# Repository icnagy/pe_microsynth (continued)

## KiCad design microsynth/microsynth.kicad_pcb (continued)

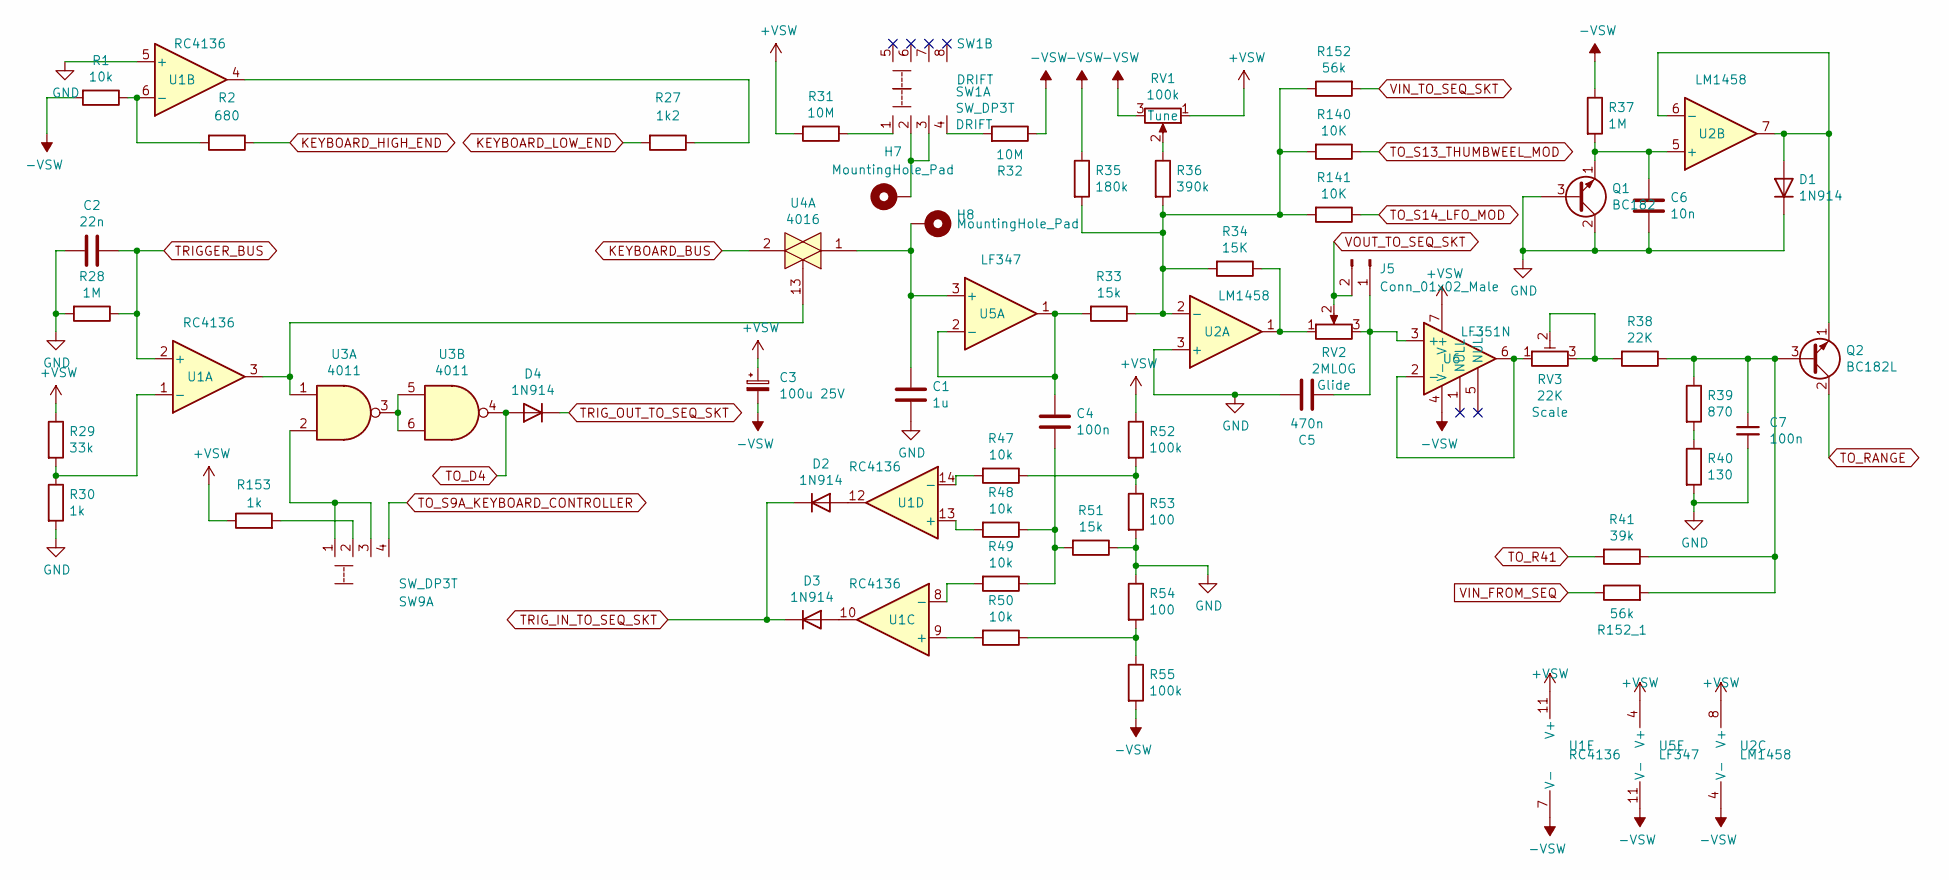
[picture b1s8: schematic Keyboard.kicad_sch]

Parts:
C1: 1u; C_Rect_L7.2mm_W7.2mm_P5.00mm_FKS2_FKP2_MKS2_MKP2
C2: 22n; C_Rect_L7.2mm_W2.5mm_P5.00mm_FKS2_FKP2_MKS2_MKP2
C3: 100u 25V; CP_Radial_D5.0mm_P2.50mm
C4, C7: 100n; C_Rect_L7.2mm_W2.5mm_P5.00mm_FKS2_FKP2_MKS2_MKP2
C5: 470n; C_Rect_L7.2mm_W4.5mm_P5.00mm_FKS2_FKP2_MKS2_MKP2
C6: 10n; C_Rect_L7.2mm_W2.5mm_P5.00mm_FKS2_FKP2_MKS2_MKP2
D1, D2, D3, D4: 1N914; D_DO-35_SOD27_P7.62mm_Horizontal
H7, H8: MountingHole_Pad; PinHeader_1x01_P2.54mm_Vertical
J5: Conn_01x02_Male; PinHeader_1x02_P2.54mm_Vertical
Q1: BC182; TO-92L_Inline_Wide
Q2: BC182L; TO-92L_Inline_Wide
R1, R47, R48, R49, R50: 10k; R_Axial_DIN0207_L6.3mm_D2.5mm_P10.16mm_Horizontal
R2: 680; R_Axial_DIN0207_L6.3mm_D2.5mm_P10.16mm_Horizontal
R27: 1k2; R_Axial_DIN0207_L6.3mm_D2.5mm_P10.16mm_Horizontal
R28, R37: 1M; R_Axial_DIN0207_L6.3mm_D2.5mm_P10.16mm_Horizontal
R29: 33k; R_Axial_DIN0207_L6.3mm_D2.5mm_P10.16mm_Horizontal
R30, R153: 1k; R_Axial_DIN0207_L6.3mm_D2.5mm_P10.16mm_Horizontal
R31, R32: 10M; R_Axial_DIN0207_L6.3mm_D2.5mm_P10.16mm_Horizontal
R33, R51: 15k; R_Axial_DIN0207_L6.3mm_D2.5mm_P10.16mm_Horizontal
R34: 15K; R_Axial_DIN0207_L6.3mm_D2.5mm_P10.16mm_Horizontal
R35: 180k; R_Axial_DIN0207_L6.3mm_D2.5mm_P10.16mm_Horizontal
R36: 390k; R_Axial_DIN0207_L6.3mm_D2.5mm_P10.16mm_Horizontal
R38: 22K; R_Axial_DIN0207_L6.3mm_D2.5mm_P10.16mm_Horizontal
R39: 870; R_Axial_DIN0207_L6.3mm_D2.5mm_P10.16mm_Horizontal
R40: 130; R_Axial_DIN0207_L6.3mm_D2.5mm_P10.16mm_Horizontal
R41: 39k; R_Axial_DIN0207_L6.3mm_D2.5mm_P10.16mm_Horizontal
R52, R55: 100k; R_Axial_DIN0207_L6.3mm_D2.5mm_P10.16mm_Horizontal
R53, R54: 100; R_Axial_DIN0207_L6.3mm_D2.5mm_P10.16mm_Horizontal
R140, R141: 10K; R_Axial_DIN0207_L6.3mm_D2.5mm_P10.16mm_Horizontal
R152, R152_1: 56k; R_Axial_DIN0207_L6.3mm_D2.5mm_P10.16mm_Horizontal
RV1: 100k; Potentiometer_Bourns_3296W_Vertical
RV2: 2MLOG; Pot_16mm_NoDet_RV16AF-4A
RV3: 22K; Potentiometer_Bourns_3296W_Vertical
SW1: SW_DP3T; 11-SS-23-832C
SW9: TRIGGER; 11-SS-23-832C
U1: RC4136; DIP-14_W7.62mm_LongPads
U2: LM1458; DIP-8_W7.62mm_LongPads
U3: 4011; DIP-14_W7.62mm_LongPads
U4: 4016; DIP-14_W7.62mm_LongPads
U5: LF347; DIP-14_W7.62mm_LongPads
U6: LF351N; DIP-8_W7.62mm_LongPads

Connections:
+VSW: C3.1, R29.1, R31.2, R52.1, R153.1, RV1.1, U1.11 (V+), U2.8 (V+), U5.4 (V+), U6.7 (V+); also elsewhere on the board
-VSW: C3.2, R1.2, R32.1, R35.1, R37.1, R55.2, RV1.3, U1.7 (V-), U2.4 (V-), U5.11 (V-), U6.4 (V-); also elsewhere on the board
GND: C1.2, C2.2, C5.2, C6.2, C7.2, D1.1 (K), Q1.2 (C), Q1.3 (B), R28.2, R30.2, R40.2, R51.1, R53.2, R54.1, U1.5 (+), U2.3 (+); also elsewhere on the board
KEYBOARD_BUS: U4.2; also elsewhere on the board
KEYBOARD_HIGH_END: R2.1; also elsewhere on the board
KEYBOARD_LOW_END: R27.2; also elsewhere on the board
unnamed: C1.1, H8.1, U4.1, U5.3 (+)
unnamed: C4.1, R33.2, U5.1, U5.2 (-)
unnamed: C4.2, R48.1, R49.1, R51.2
unnamed: C5.1, J5.1, RV2.3, U6.3 (+)
unnamed: C6.1, Q1.1 (E), R37.2, U2.5 (+)
unnamed: C7.1, Q2.3 (B), R38.1, R39.1, R41.1, R152_1.2
unnamed: D1.2 (A), Q2.1 (E), U2.6 (-), U2.7
unnamed: D2.2 (A), U1.12
unnamed: D3.2 (A), U1.10
unnamed: H7.1, SW1.2, SW1.3
unnamed: R1.1, R2.2, U1.6 (-)
unnamed: R27.1, U1.4
unnamed: R29.2, R30.1, U1.1 (-)
unnamed: R31.1, SW1.1
unnamed: R32.2, SW1.4
unnamed: R34.1, RV2.1, U2.1
unnamed: R36.1, RV1.2
unnamed: R38.2, RV3.2, RV3.3
unnamed: R39.2, R40.1
unnamed: R47.1, R52.2, R53.1
unnamed: R47.2, U1.14 (-)
unnamed: R48.2, U1.13 (+)
unnamed: R49.2, U1.8 (-)
unnamed: R50.1, R54.2, R55.1
unnamed: R50.2, U1.9 (+)
unnamed: R33.1, R34.2, R35.2, R36.2, R140.2, R141.2, R152.1, U2.2 (-)
unnamed: R153.2, SW9.2
unnamed: RV3.1, U6.2 (-), U6.6
unnamed: SW9.1, SW9.3, U3.2
unnamed: U1.3, U3.1, U4.13
unnamed: U3.3, U3.5, U3.6
S5_VCO2: SW9.4; also elsewhere on the board
TO_D4: D4.2 (A), U3.4; also elsewhere on the board
TO_KBD_R140: R140.1; also elsewhere on the board
TO_KBD_R141: R141.1; also elsewhere on the board
TO_R41: R41.2; also elsewhere on the board
TO_RANGE: Q2.2 (C); also elsewhere on the board
TRIGGER_BUS: C2.1, R28.1, U1.2 (+); also elsewhere on the board
TRIG_IN_TO_SEQ_SKT: D2.1 (K), D3.1 (K); also elsewhere on the board
TRIG_OUT_TO_SEQ_SKT: D4.1 (K); also elsewhere on the board
VIN_FROM_SEQ: R152_1.1; also elsewhere on the board
VIN_TO_SEQ_SKT: R152.2; also elsewhere on the board
VOUT_TO_SEQ_SKT: J5.2, RV2.2; also elsewhere on the board

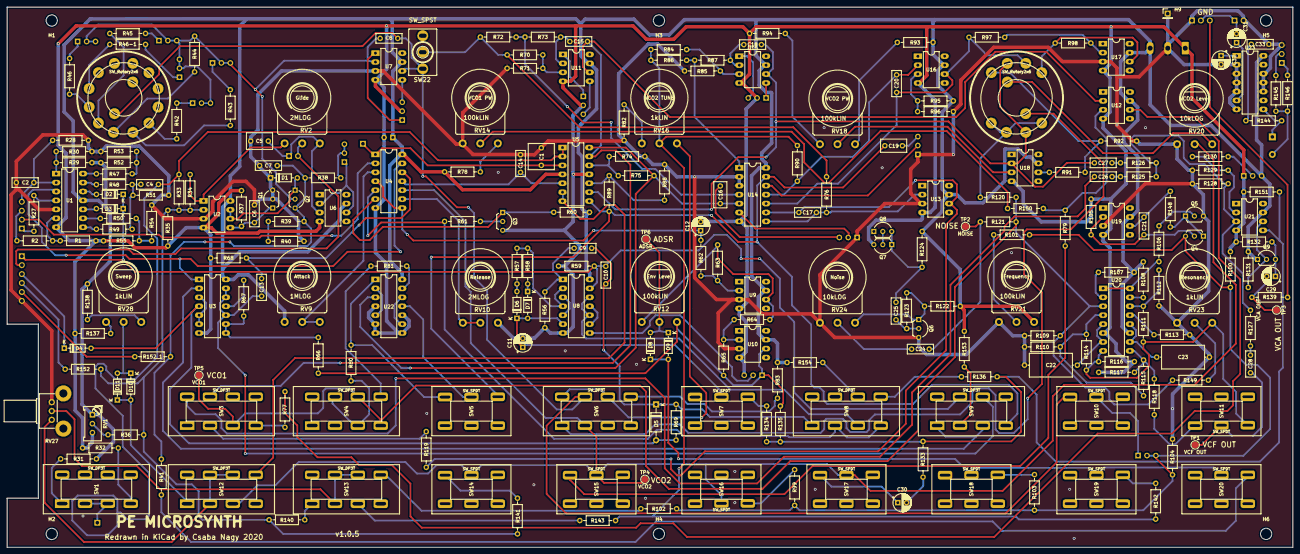
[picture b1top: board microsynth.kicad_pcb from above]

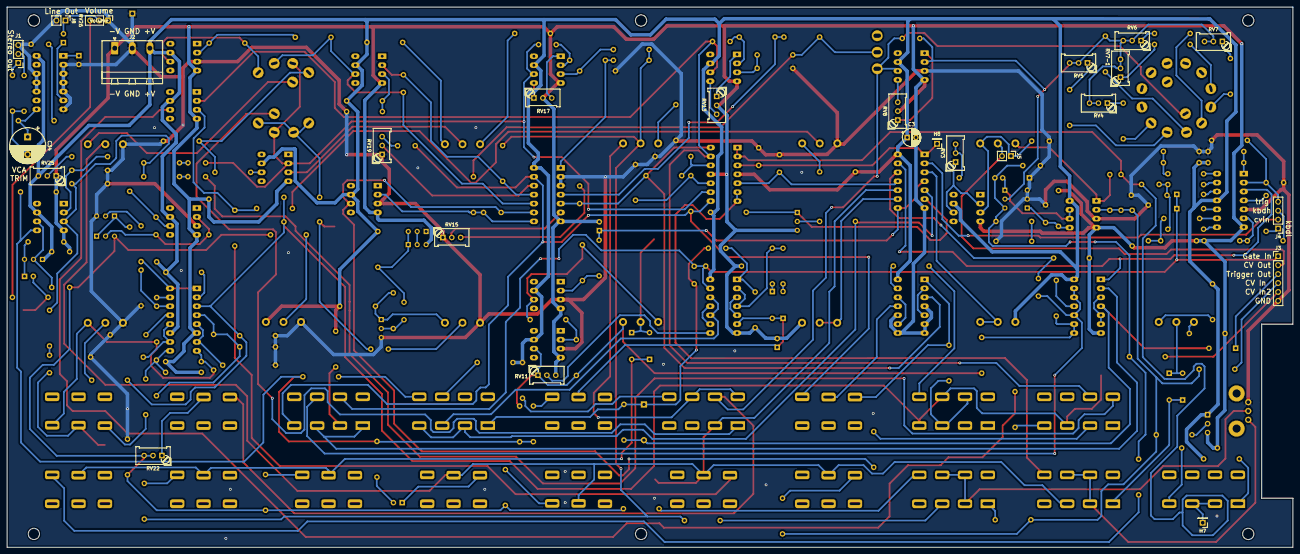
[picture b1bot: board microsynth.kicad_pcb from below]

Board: 2 copper layers, 365.8 x 153.7 mm, 280 parts (25 on the bottom side), 208 nets.

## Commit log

2020-03-30 Footprints
2020-04-01 Footprints 2
2020-04-01 Hacking together the footprints
2020-04-03 All components placed on PCB
2020-04-03 Add front panel design
2020-04-03 Aligned switches and pots
2020-04-06 Laying out pcb
2020-04-08 Laying out pcb ...
2020-04-09 Add datasheets
2020-04-13 Layout...
2020-04-17 Add 3d models
2020-04-17 Change switch footprints
2020-04-18 Layout...-11
2020-04-19 Layout...-7
2020-04-20 Layout...-3
2020-04-20 Move connectors to back
2020-04-22 V1.0.0b
2020-04-22 Replacing dp3p switches 1.
2020-04-22 Replacing dp3p switches 2.
2020-04-25 Replacing SPDT switches
2020-04-26 Replace all SPDT switches
2020-04-26 Tidy up, 1 solder wire
2020-04-26 Tidy up, name switches, proper footprints for all trimmers
2020-04-26 Replace switches in schematic, add extra octave to VCO
2020-04-26 Update datasheet for SW2
2020-04-28 Replace SW21 with 3p4t tayda
2020-04-29 Proper capacitor footprints
2020-04-30 Label pots
2020-05-03 Added pots datasheets, tidy up U9 U10 labels
2020-05-03 Reroute a long track
2020-05-03 Add new V input
2020-05-03 Add VCO2 on/off toggle, faceplace 3d, and new faceplate version
2020-05-03 Add thumbwheel scad file
2020-05-04 Front panel v3
2020-05-04 Text on pcb and local footprints
2020-05-04 Add new front panel to 3d view
2020-05-06 gitignore and thumbwheel update
2020-05-06 Update thumbwheel to parametric
2020-05-09 New 3d models
2020-05-09 Clean up repo
2020-05-10 Tidy up layout
2020-05-10 More layout/repo tidy up
2020-05-10 Replace front panel
2020-05-10 Replace thumbwheel and cleanup
2020-05-10 Front panel update
2020-05-13 Update gitignore
2020-05-13 Replace dodgy parts 1458, 4136 & LF351s
2020-05-14 Proper mounting holes
2020-05-17 Replace DP3T footprint, proper wire pads
2020-05-17 Add tayda slide switch datasheets (DPDT & DP3T)
2020-05-17 Add 4136 datasheet
2020-05-17 Add tayda rotary switch datasheet
2020-05-17 Add thumbwheel datasheet and 3d model
2020-05-17 Replace all switches with tayda footprint
2020-05-21 Consolidate switches
2020-05-26 Consolidate all(?) switches
2020-06-02 Update tayda switch footprints
2020-06-04 Update tayda rotary switch footprints and layout
2020-06-04 Adjust track widths
2020-06-04 Tidy up
2020-06-05 Copper fill GND
2020-06-05 Add tayda rotary switch footprints (again)
2020-06-05 Update front panel
2020-06-07 Add test points
2020-06-25 Remove smd footprints, create and assign power/default tracks, tidy up ground planes
2020-06-25 More ground plane tidy ups
2020-08-01 Update switch footprints with bigger pads
2020-08-01 Update switch footprints with bigger pads again
2020-08-02 Improve layout
2020-08-19 Add GND test point, add gnd to CV/Gate In/Out connector
2020-08-23 Add components list (jpg)
2020-08-23 Remove FPD exports
2020-08-23 Update documentation
2020-08-23 Update image links, label Tune pot
2020-08-24 v1.0.0
2020-08-24 Fix output amp
2020-08-25 Replace IC1 with LM348, update component values
2020-09-01 Annotate schematic
2020-09-02 Remove keyboard stuff
2020-09-02 Clean up and reroute
2020-09-08 Put test point values to silkskreen
2020-09-09 Enable Back Silk Screen
2020-09-09 Replace power connector with 4 pin molex p3.96
2020-09-09 Replace power connector, optimize layout around it
2020-09-09 Replace power connector (again) with a plug-in style, remove redundant global label
2020-09-15 Optimize layout around U1
2020-09-25 Optimise layout around output
2020-11-08 Add ground fills
2020-11-23 v1.0.5
2023-02-16 Update gitignore, ignore gerber outputs
2023-02-16 Not sure. Looks like stuff got moved around
2023-02-19 Upgrade to KiCad 7
2023-05-29 Remove obsolete files
2023-05-29 Refill zones in 7.0.5
